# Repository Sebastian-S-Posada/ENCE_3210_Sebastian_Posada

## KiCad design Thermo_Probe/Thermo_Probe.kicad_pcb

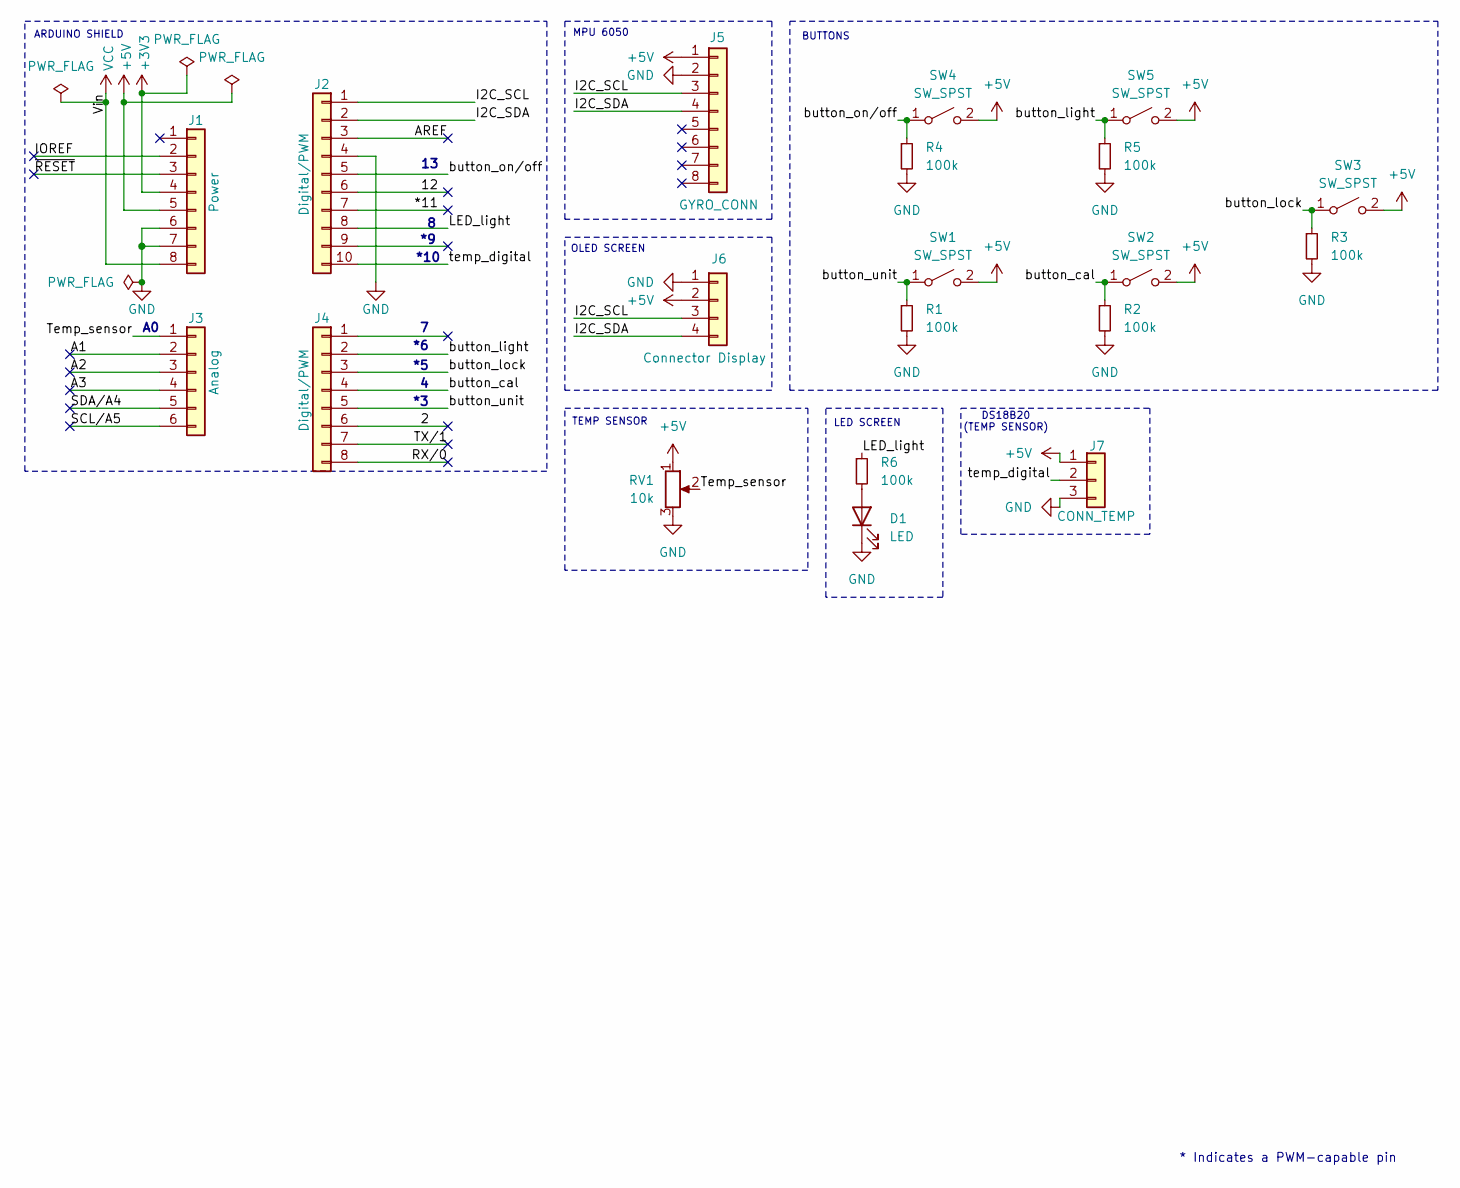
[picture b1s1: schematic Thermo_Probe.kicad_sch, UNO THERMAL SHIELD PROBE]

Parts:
D1: LED; LED_D5.0mm
J1: Power; PinSocket_1x08_P2.54mm_Vertical
J2: Digital/PWM; PinSocket_1x10_P2.54mm_Vertical
J3: Analog; PinSocket_1x06_P2.54mm_Vertical
J4: Digital/PWM; PinSocket_1x08_P2.54mm_Vertical
J5: GYRO_CONN; PinSocket_1x08_P2.54mm_Vertical
J6: Connector Display; PinSocket_1x04_P2.54mm_Vertical
J7: CONN_TEMP; JST_XH_B3B-XH-A_1x03_P2.50mm_Vertical
R1, R2, R3, R4, R5, R6: 100k; R_Axial_DIN0207_L6.3mm_D2.5mm_P10.16mm_Horizontal
RV1: 10k; Potentiometer_Bourns_3386P_Vertical
SW1, SW2, SW3, SW4, SW5: SW_SPST; SW_PUSH_6mm

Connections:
+3V3: J1.4
+5V: J1.5, J5.1, J6.2, J7.1, RV1.1, SW1.2 (B), SW2.2 (B), SW3.2 (B), SW4.2 (B), SW5.2 (B)
/2: J4.6
/12: J2.6
/*11: J2.7
/A1: J3.2
/A2: J3.3
/A3: J3.4
/AREF: J2.3
/I2C_SCL: J2.1, J5.3, J6.3
/I2C_SDA: J2.2, J5.4, J6.4
/IOREF: J1.2
/LED_light: J2.8, R6.1
/RX/0: J4.8
/SCL/A5: J3.6
/SDA/A4: J3.5
/TX/1: J4.7
/Temp_sensor: J3.1, RV1.2
/button_cal: J4.4, R2.1, SW2.1 (A)
/button_light: J4.2, R5.1, SW5.1 (A)
/button_lock: J4.3, R3.1, SW3.1 (A)
/button_on/off: J2.5, R4.1, SW4.1 (A)
/button_unit: J4.5, R1.1, SW1.1 (A)
/temp_digital: J2.10, J7.2
/~RESET: J1.3
GND: D1.1 (K), J1.6, J1.7, J2.4, J5.2, J6.1, J7.3, R1.2, R2.2, R3.2, R4.2, R5.2, RV1.3
unnamed: D1.2 (A), R6.2
VCC: J1.8

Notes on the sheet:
LED SCREEN
DS18B20 (TEMP SENSOR)
BUTTONS
*10
ARDUINO SHIELD
TEMP SENSOR
OLED SCREEN
MPU 6050
* Indicates a PWM-capable pin

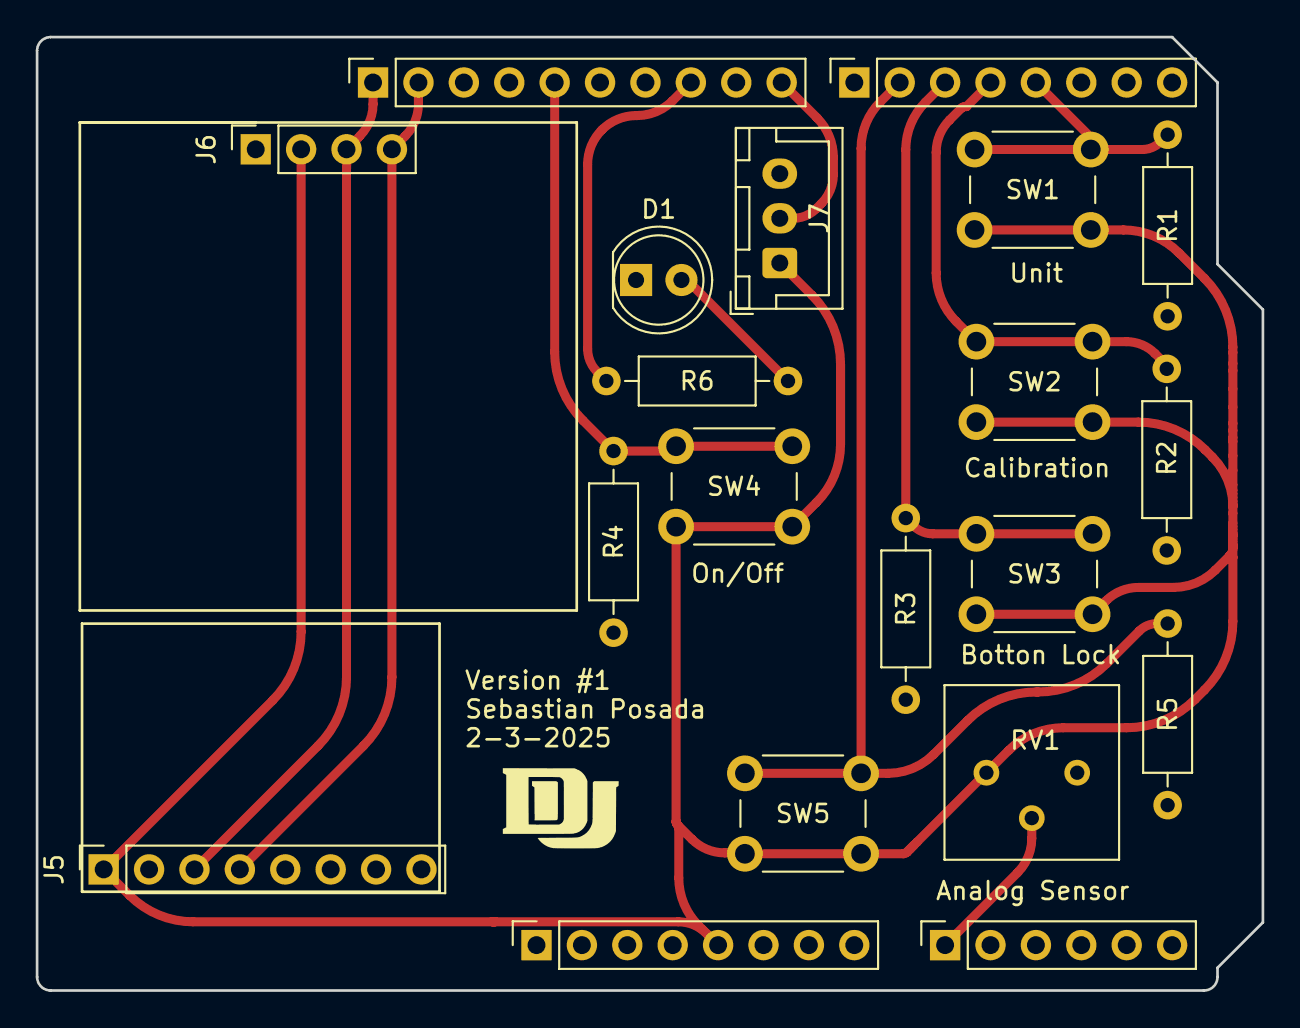
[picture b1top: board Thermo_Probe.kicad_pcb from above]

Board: 2 copper layers, 68.6 x 53.3 mm, 20 parts (0 on the bottom side), 13 nets.

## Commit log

2025-01-10 LAB 1 Test
2025-01-24 LAB#2
2025-01-31 LAB#3
2025-02-04 Probe
